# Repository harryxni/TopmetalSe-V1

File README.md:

# TopmetalSe-V1
This repo stores almost all of the info to run and understand the TopmetalSe

The directories here should be pretty self-explanatory honestly. 

If you want to learn how to run the chip, please look at Hardware and Firmware.

If you want to learn how well the chip performs and see examples, please look at Results.

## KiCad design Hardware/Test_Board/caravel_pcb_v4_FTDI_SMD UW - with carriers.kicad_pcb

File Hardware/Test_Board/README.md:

# Annotated PCB

In the annotated pcb image file, I have added some markers to explain any fixes that need to be made to the current test board. These are either where jumper cables must be soldered onto, or any components which should not be present.

On the left side of the board, the level shifters U12-U26 should not be used/soldered on. Instead, a jumper cable should be soldered between pads 3 and 4.

D4 should not be soldered on simply to remove a strong source of light which could ionize charge in the pixel array. It can useful to know if power is being supplied correctly, so use it in any initial testing phases. But, it should not be present for serious testing.

LA_Row_Clk should always be used and not Ser Tx (jumpered across).

VCCD should be connected to VCCD2 under the carrier board, so there should be a jumper wire between pins 43 and 27.

R23, R25 and R27 should not be present to prevent current flow along the voltage bias lines.

LDAC bar should always be jumpered.

The signals names for ROW and COL are actually switched. This is fixed in the FPGA software which controls these lines, but should be noted for any future iterations.

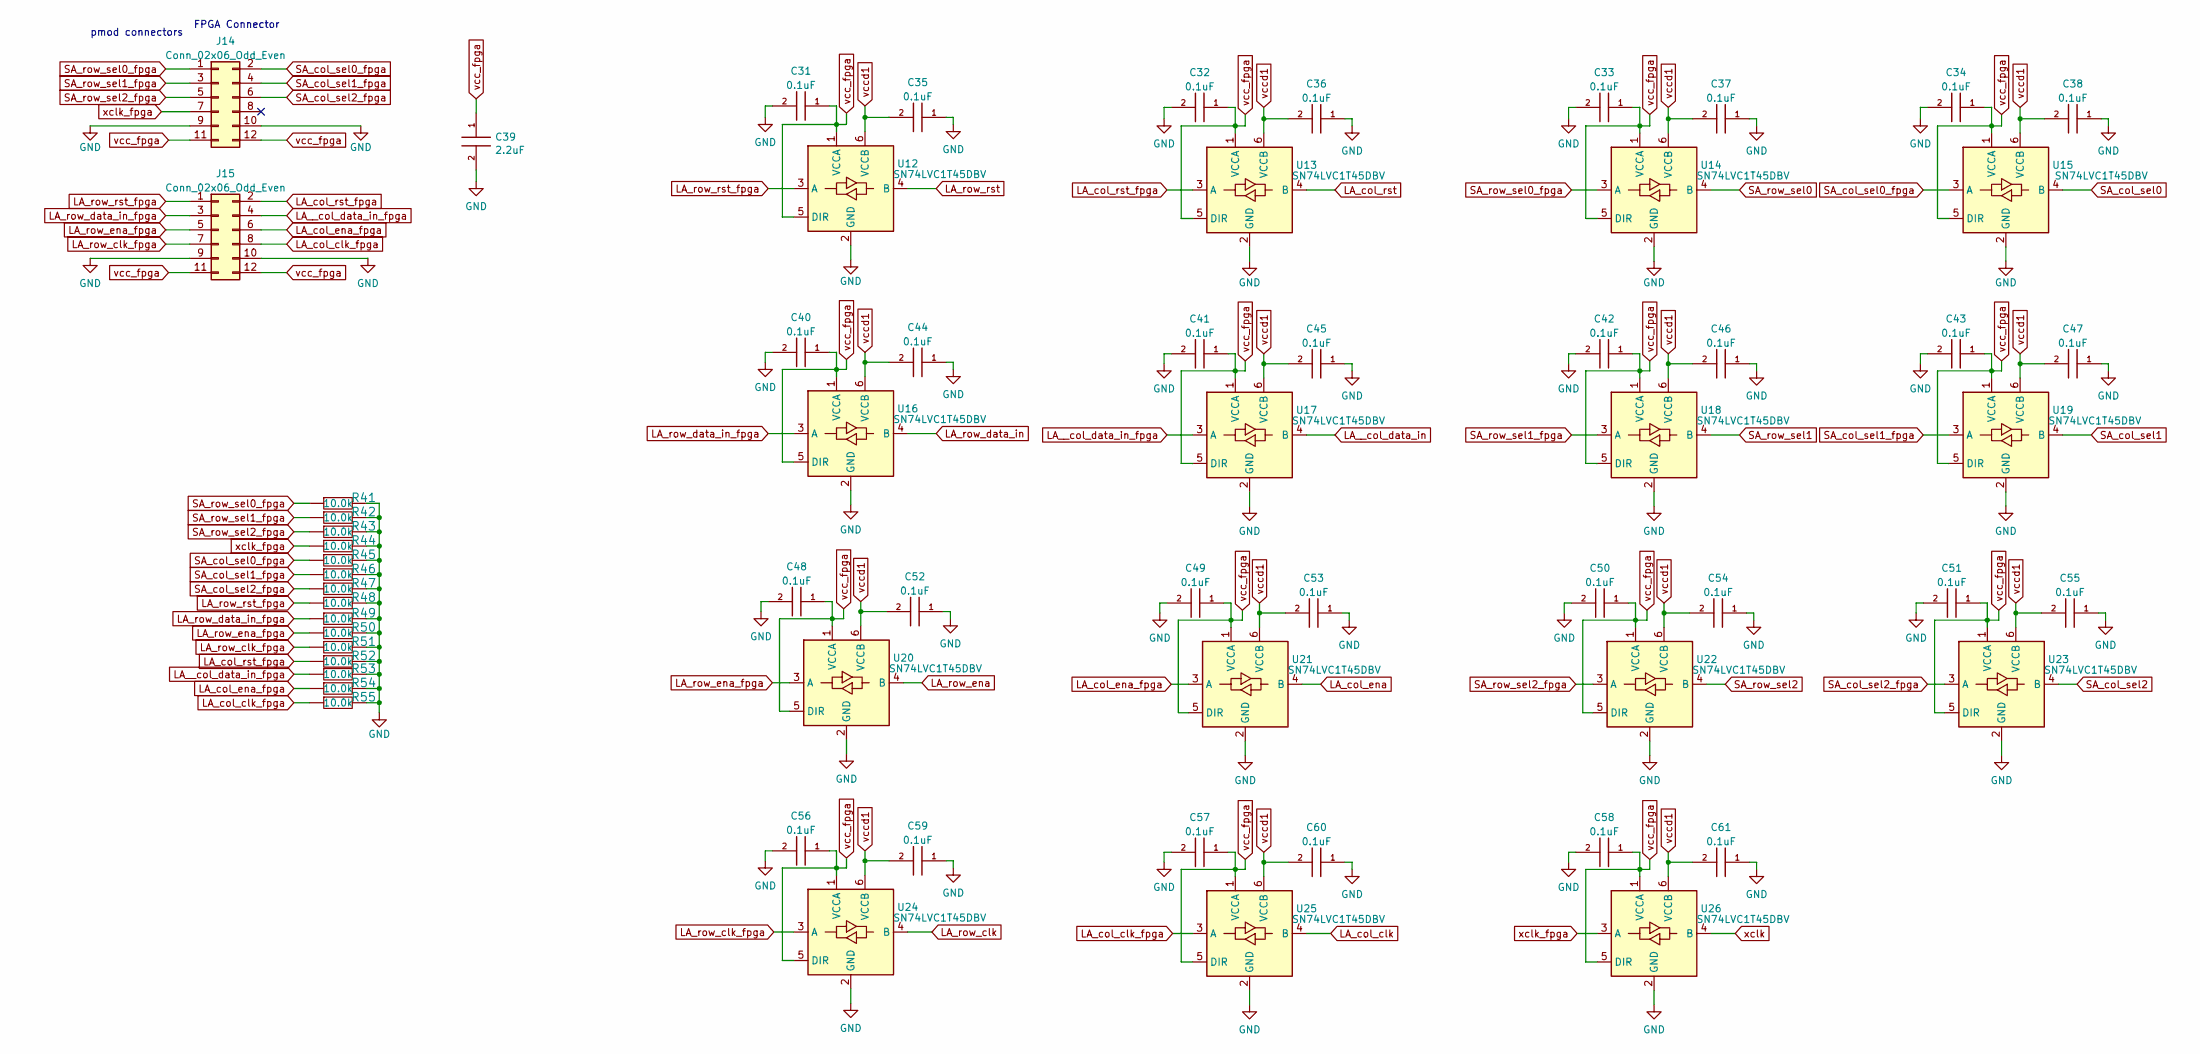
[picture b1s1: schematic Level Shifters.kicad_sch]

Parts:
C31, C32, C33, C34, C35, C36, C37, C38, C40, C41, C42, C43, C44, C45, C46, C47, C48, C49, C50, C51, C52, C53, C54, C55, C56, C57, C58, C59, C60, C61: 0.1uF; SM0603
C39: 2.2uF; SM0603
J14, J15: Conn_02x06_Odd_Even; PinHeader_2x06_P2.54mm_Horizontal
R41, R42, R43, R44, R45, R46, R47, R48, R49, R50, R51, R52, R53, R54, R55: 10.0k; SM0603
U12, U13, U14, U15, U16, U17, U18, U19, U20, U21, U22, U23, U24, U25, U26: SN74LVC1T45DBV; SOT-23-6

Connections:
LA__col_data_in: U17.4 (B); also elsewhere on the board
LA__col_data_in_fpga: J15.4, R53.1, U17.3 (A)
LA_col_clk: U25.4 (B); also elsewhere on the board
LA_col_clk_fpga: J15.8, R55.1, U25.3 (A)
LA_col_ena: U21.4 (B); also elsewhere on the board
LA_col_ena_fpga: J15.6, R54.1, U21.3 (A)
LA_col_rst: U13.4 (B); also elsewhere on the board
LA_col_rst_fpga: J15.2, R52.1, U13.3 (A)
LA_row_clk: U24.4 (B); also elsewhere on the board
LA_row_clk_fpga: J15.7, R51.1, U24.3 (A)
LA_row_data_in: U16.4 (B); also elsewhere on the board
LA_row_data_in_fpga: J15.3, R49.1, U16.3 (A)
LA_row_ena: U20.4 (B); also elsewhere on the board
LA_row_ena_fpga: J15.5, R50.1, U20.3 (A)
LA_row_rst: U12.4 (B); also elsewhere on the board
LA_row_rst_fpga: J15.1, R48.1, U12.3 (A)
SA_col_sel0: U15.4 (B); also elsewhere on the board
SA_col_sel0_fpga: J14.2, R45.1, U15.3 (A)
SA_col_sel1: U19.4 (B); also elsewhere on the board
SA_col_sel1_fpga: J14.4, R46.1, U19.3 (A)
SA_col_sel2: U23.4 (B); also elsewhere on the board
SA_col_sel2_fpga: J14.6, R47.1, U23.3 (A)
SA_row_sel0: U14.4 (B); also elsewhere on the board
SA_row_sel0_fpga: J14.1, R41.1, U14.3 (A)
SA_row_sel1: U18.4 (B); also elsewhere on the board
SA_row_sel1_fpga: J14.3, R42.1, U18.3 (A)
SA_row_sel2: U22.4 (B); also elsewhere on the board
SA_row_sel2_fpga: J14.5, R43.1, U22.3 (A)
vcc_fpga: C31.1, C32.1, C33.1, C34.1, C39.1, C40.1, C41.1, C42.1, C43.1, C48.1, C49.1, C50.1, C51.1, C56.1, C57.1, C58.1, J14.11, J14.12, J15.11, J15.12, U12.1 (VCCA), U12.5 (DIR), U13.1 (VCCA), U13.5 (DIR), U14.1 (VCCA), U14.5 (DIR), U15.1 (VCCA), U15.5 (DIR), U16.1 (VCCA), U16.5 (DIR), U17.1 (VCCA), U17.5 (DIR), U18.1 (VCCA), U18.5 (DIR), U19.1 (VCCA), U19.5 (DIR), U20.1 (VCCA), U20.5 (DIR), U21.1 (VCCA), U21.5 (DIR), U22.1 (VCCA), U22.5 (DIR), U23.1 (VCCA), U23.5 (DIR), U24.1 (VCCA), U24.5 (DIR), U25.1 (VCCA), U25.5 (DIR), U26.1 (VCCA), U26.5 (DIR)
vccd: C35.2, C36.2, C37.2, C38.2, C44.2, C45.2, C46.2, C47.2, C52.2, C53.2, C54.2, C55.2, C59.2, C60.2, C61.2, U12.6 (VCCB), U13.6 (VCCB), U14.6 (VCCB), U15.6 (VCCB), U16.6 (VCCB), U17.6 (VCCB), U18.6 (VCCB), U19.6 (VCCB), U20.6 (VCCB), U21.6 (VCCB), U22.6 (VCCB), U23.6 (VCCB), U24.6 (VCCB), U25.6 (VCCB), U26.6 (VCCB); also elsewhere on the board
xclk: U26.4 (B); also elsewhere on the board
xclk_fpga: J14.7, R44.1, U26.3 (A)

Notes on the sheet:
pmod connectors
FPGA Connector

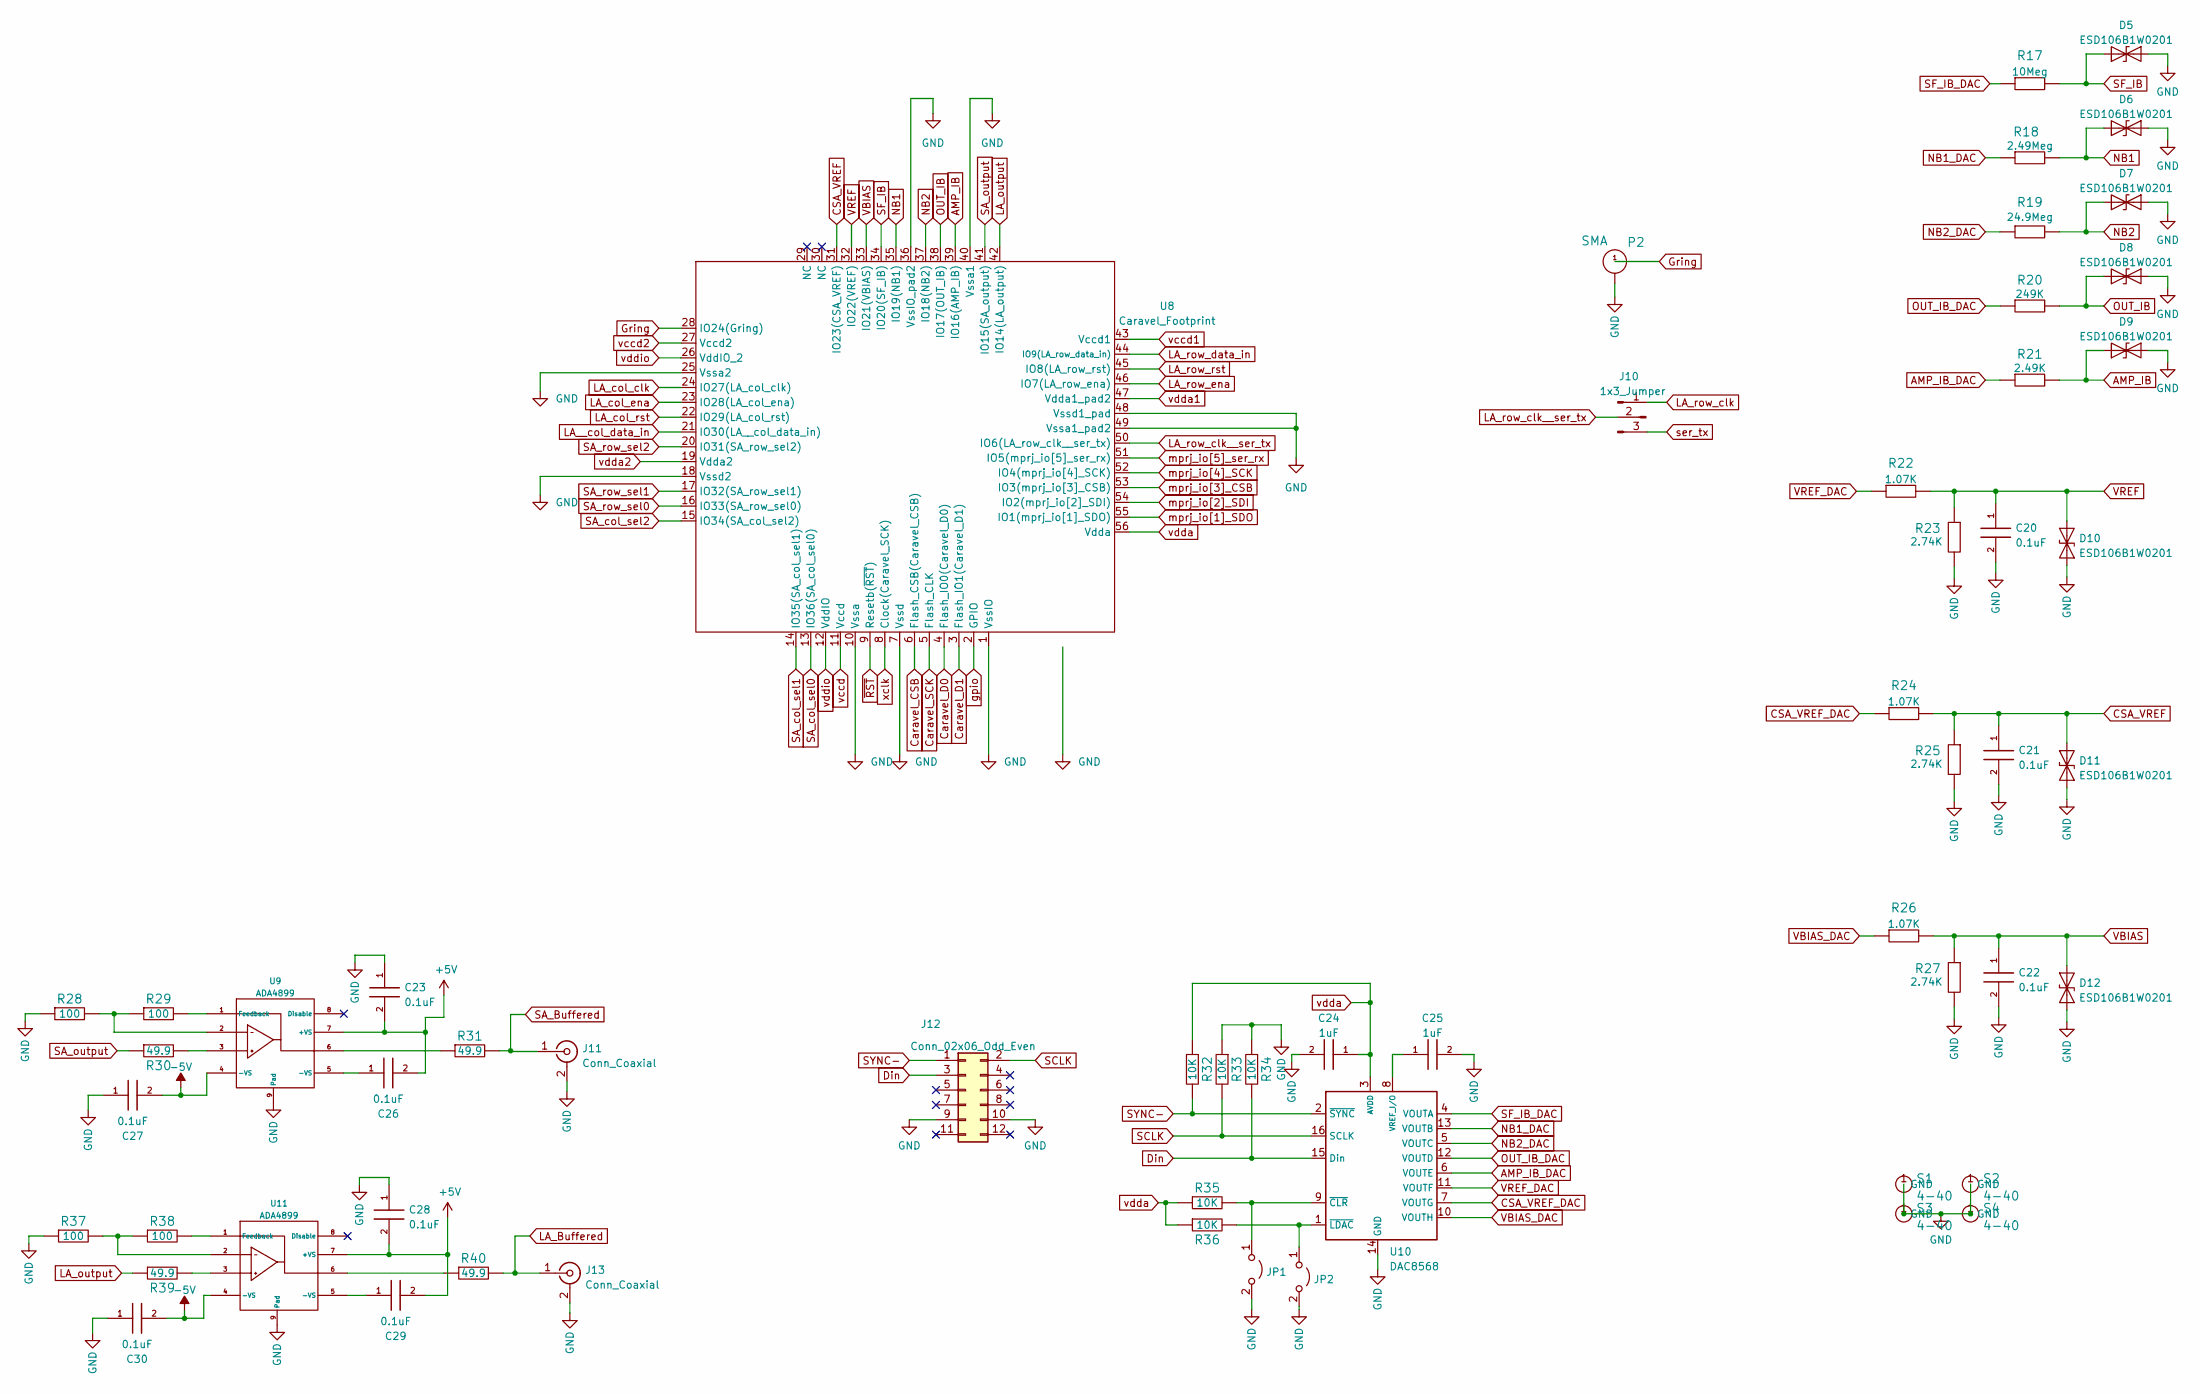
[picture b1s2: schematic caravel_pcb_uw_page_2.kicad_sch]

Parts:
C20, C21, C22, C23, C26, C27, C28, C29, C30: 0.1uF; SM0603
C24, C25: 1uF; SM0603
D5, D6, D7, D8, D9, D10, D11, D12: ESD106B1W0201; D_SOD-923
J10: 1x3_Jumper; SIL-3
J11, J13: Conn_Coaxial; SMA
J12: Conn_02x06_Odd_Even; PinHeader_2x06_P2.54mm_Horizontal
JP1, JP2: Jumper_2_Open; SIL-2
P2: SMA
R17: 10Meg; SM0603
R18: 2.49Meg; SM0603
R19: 24.9Meg; SM0603
R20: 249K; SM0603
R21: 2.49K; SM0603
R22, R24, R26: 1.07K; SM0603
R23, R25, R27: 2.74K; SM0603
R28, R29, R37, R38: 100; SM0603
R30, R31, R39, R40: 49.9; SM0603
R32, R33, R34, R35, R36: 10K; SM0603
S1, S2, S3, S4: 4-40; 4-40_Reduced
U8: Caravel_Footprint; Caravel_Carrier_Footprint
U9, U11: ADA4899; SO-8_EP
U10: DAC8568; TSSOP-16_4.4x5mm_P0.65mm

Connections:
AMP_IB: D9.1 (A1), R21.2, U8.39 (IO16(AMP_IB))
AMP_IB_DAC: R21.1, U10.6 (VOUTE)
CSA_VREF: C21.1, D11.1 (A1), R24.2, R25.1, U8.31 (IO23(CSA_VREF))
CSA_VREF_DAC: R24.1, U10.7 (VOUTG)
Caravel_CSB: U8.6 (Flash_CSB(Caravel_CSB)); also elsewhere on the board
Caravel_D0: U8.4 (Flash_IO0(Caravel_D0)); also elsewhere on the board
Caravel_D1: U8.3 (Flash_IO1(Caravel_D1)); also elsewhere on the board
Caravel_SCK: U8.5 (Flash_CLK); also elsewhere on the board
Din: J12.3, R34.2, U10.15 (Din)
Gring: P2.1, U8.28 (IO24(Gring))
LA_Buffered: J13.1 (In), R40.2
LA__col_data_in: U8.21 (IO30(LA__col_data_in)); also elsewhere on the board
LA_col_clk: U8.24 (IO27(LA_col_clk)); also elsewhere on the board
LA_col_ena: U8.23 (IO28(LA_col_ena)); also elsewhere on the board
LA_col_rst: U8.22 (IO29(LA_col_rst)); also elsewhere on the board
LA_output: R39.1, U8.42 (IO14(LA_output))
LA_row_clk: J10.1; also elsewhere on the board
LA_row_clk__ser_tx: J10.2, U8.50 (IO6(LA_row_clk__ser_tx))
LA_row_data_in: U8.44 (IO9(LA_row_data_in)); also elsewhere on the board
LA_row_ena: U8.46 (IO7(LA_row_ena)); also elsewhere on the board
LA_row_rst: U8.45 (IO8(LA_row_rst)); also elsewhere on the board
NB1: D6.1 (A1), R18.2, U8.35 (IO19(NB1))
NB1_DAC: R18.1, U10.13 (VOUTB)
NB2: D7.1 (A1), R19.2, U8.37 (IO18(NB2))
NB2_DAC: R19.1, U10.5 (VOUTC)
unnamed: C25.1, U10.8 (VREF_I/O)
unnamed: C26.1, U9.5 (-VS)
unnamed: C29.1, U11.5 (-VS)
unnamed: JP1.1 (A), R35.2, U10.9 (~CLR)
unnamed: JP2.1 (A), R36.2, U10.1 (~LDAC)
unnamed: R28.2, R29.1, U9.2
unnamed: R29.2, U9.1 (Feedback)
unnamed: R30.2, U9.3
unnamed: R31.1, U9.6
unnamed: R37.2, R38.1, U11.2
unnamed: R38.2, U11.1 (Feedback)
unnamed: R39.2, U11.3
unnamed: R40.1, U11.6
OUT_IB: D8.1 (A1), R20.2, U8.38 (IO17(OUT_IB))
OUT_IB_DAC: R20.1, U10.12 (VOUTD)
SA_Buffered: J11.1 (In), R31.2
SA_col_sel0: U8.13 (IO36(SA_col_sel0)); also elsewhere on the board
SA_col_sel1: U8.14 (IO35(SA_col_sel1)); also elsewhere on the board
SA_col_sel2: U8.15 (IO34(SA_col_sel2)); also elsewhere on the board
SA_output: R30.1, U8.41 (IO15(SA_output))
SA_row_sel0: U8.16 (IO33(SA_row_sel0)); also elsewhere on the board
SA_row_sel1: U8.17 (IO32(SA_row_sel1)); also elsewhere on the board
SA_row_sel2: U8.20 (IO31(SA_row_sel2)); also elsewhere on the board
SCLK: J12.2, R33.2, U10.16 (SCLK)
SF_IB: D5.1 (A1), R17.2, U8.34 (IO20(SF_IB))
SF_IB_DAC: R17.1, U10.4 (VOUTA)
SYNC-: J12.1, R32.2, U10.2 (~SYNC)
USB_CS1: U8.53 (IO3(mprj_io[3]_CSB)); also elsewhere on the board
USB_SCK_TXD: U8.52 (IO4(mprj_io[4]_SCK)); also elsewhere on the board
USB_SI: U8.55 (IO1(mprj_io[1]_SDO)); also elsewhere on the board
USB_SO_RXD: U8.54 (IO2(mprj_io[2]_SDI)); also elsewhere on the board
VBIAS: C22.1, D12.1 (A1), R26.2, R27.1, U8.33 (IO21(VBIAS))
VBIAS_DAC: R26.1, U10.10 (VOUTH)
VREF: C20.1, D10.1 (A1), R22.2, R23.1, U8.32 (IO22(VREF))
VREF_DAC: R22.1, U10.11 (VOUTF)
gpio: U8.2 (GPIO); also elsewhere on the board
mprj_io[5]_ser_rx: U8.51 (IO5(mprj_io[5]_ser_rx)); also elsewhere on the board
ser_tx: J10.3; also elsewhere on the board
vccd: U8.11 (Vccd), U8.43 (Vccd1); also elsewhere on the board
vccd2: U8.27 (Vccd2)
vdda1: U8.47 (Vdda1_pad2)
vdda2: U8.19 (Vdda2)
xclk: U8.8 (Clock(Caravel_SCK)); also elsewhere on the board
~RST: U8.9 (Resetb(~RST)); also elsewhere on the board

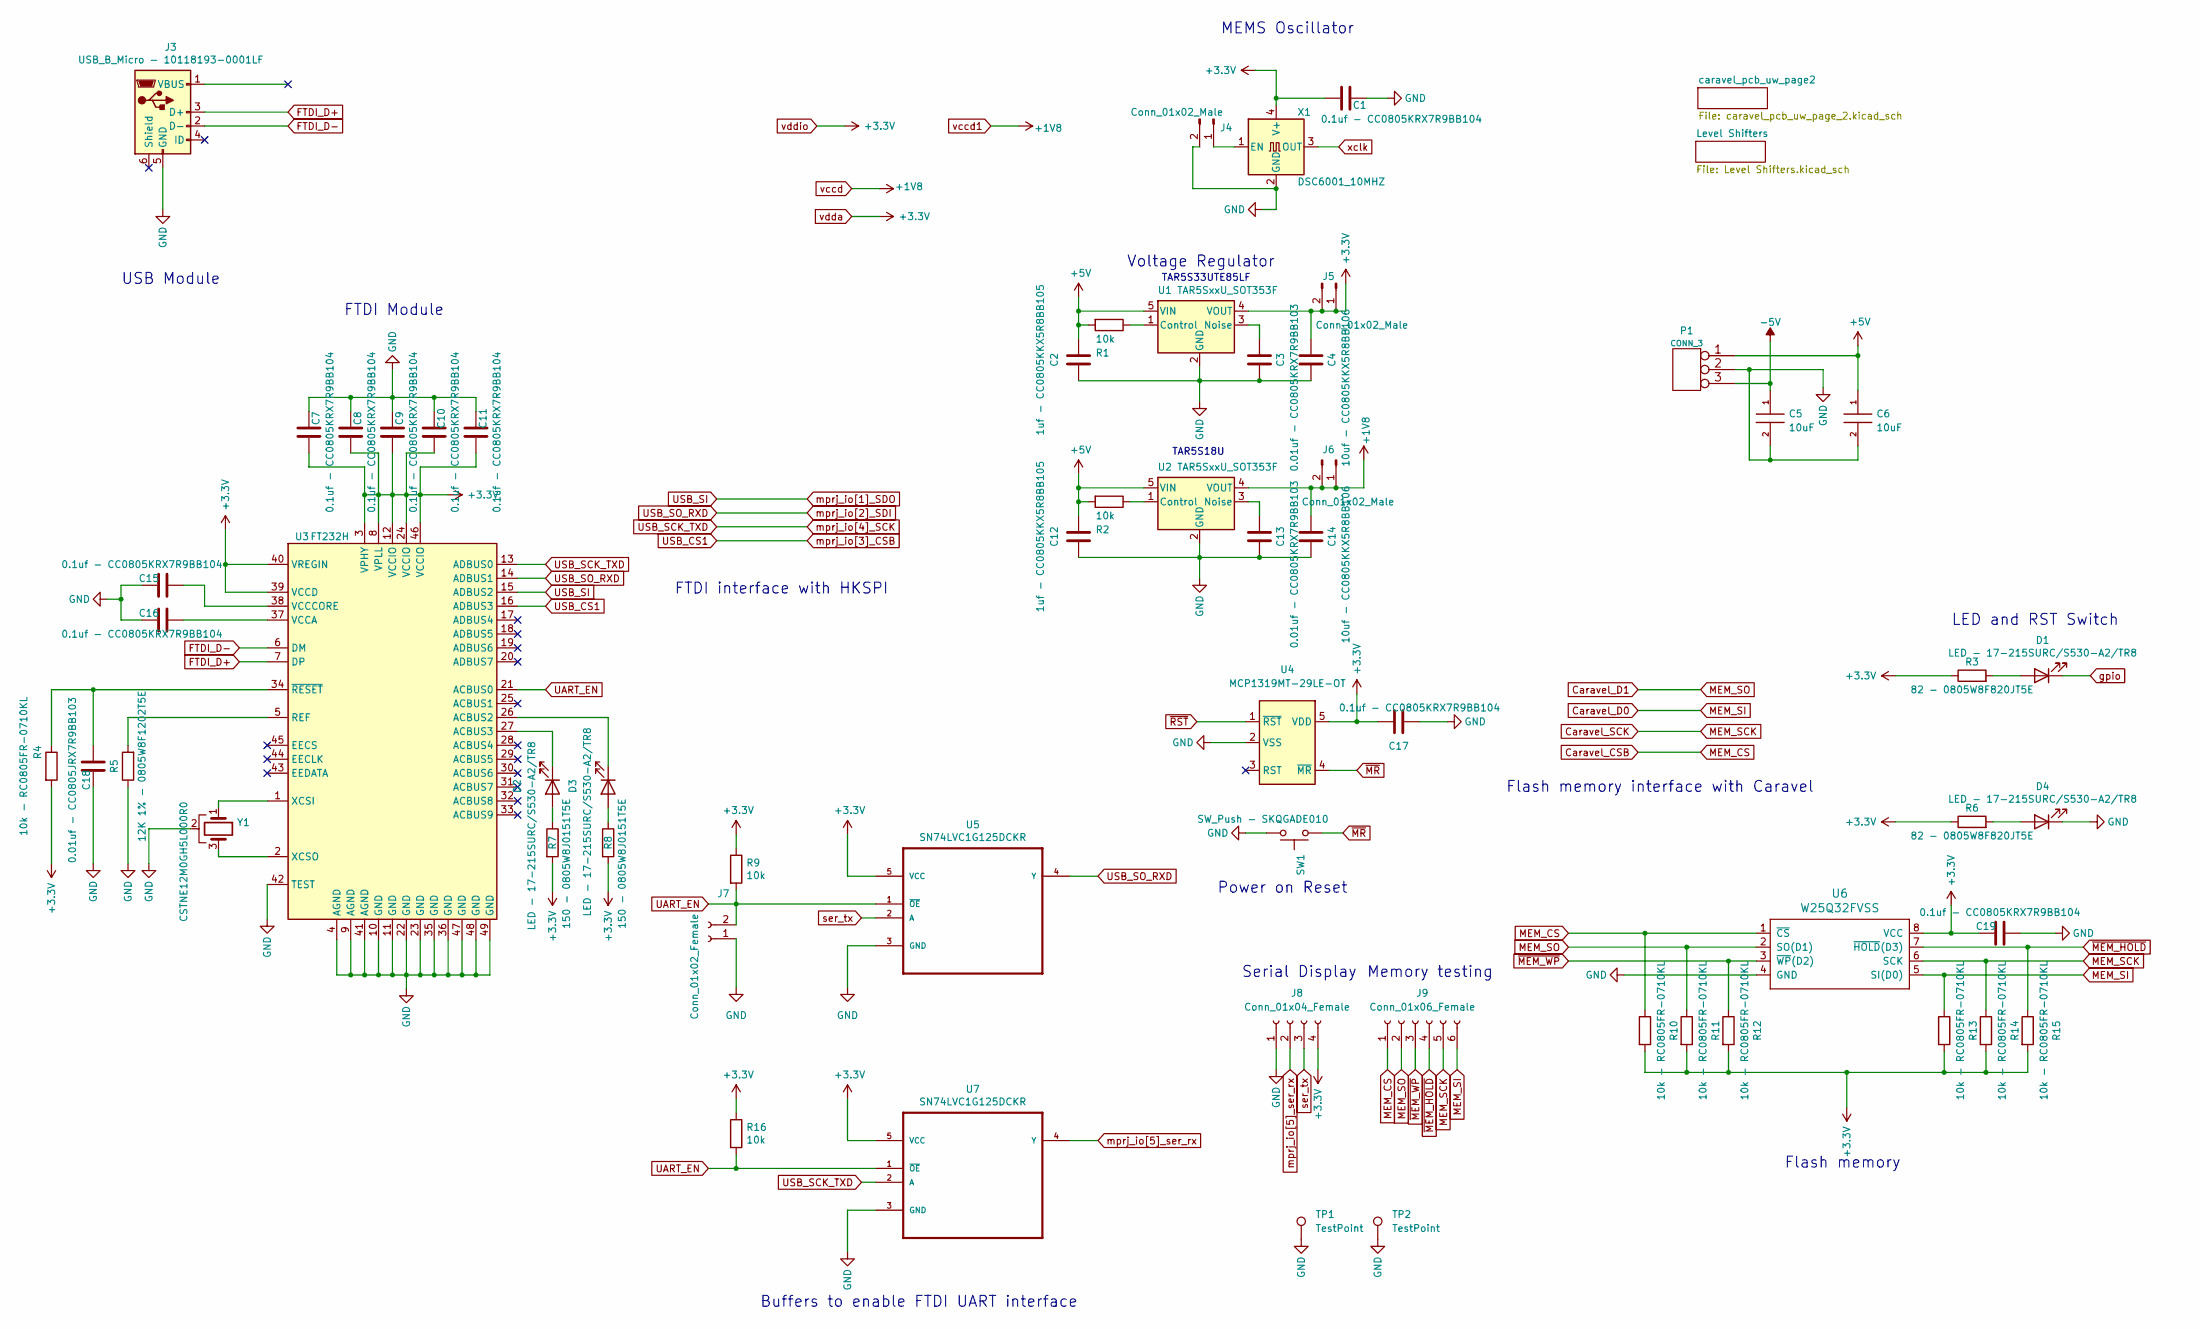
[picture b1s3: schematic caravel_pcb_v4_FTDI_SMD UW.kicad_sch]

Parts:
C1, C7, C8, C10, C11, C15, C16, C17, C19: 0.1uf - CC0805KRX7R9BB104; SM0603
C2, C12: 1uf - CC0805KKX5R8BB105; SM0603
C3, C13: 0.01uf - CC0805KRX7R9BB103; SM0603
C4, C14: 10uf - CC0805KKX5R8BB106; SM0603
C5, C6: 10uF; SM0603
C9: 0.1uf - CC0805KRX7R9BB104; SM0402
C18: 0.01uf - CC0805JRX7R9BB103; SM0603
D1, D2, D3, D4: LED - 17-215SURC/S530-A2/TR8; LED_1206_3216Metric
J3: USB_B_Micro - 10118193-0001LF; FCI_10118193-0001LF
J4, J5, J6: Conn_01x02_Male; PinHeader_1x02_P2.54mm_Vertical
J7: Conn_01x02_Female; PinHeader_1x02_P2.54mm_Vertical
J8: Conn_01x04_Female; PinHeader_1x04_P2.54mm_Vertical
J9: Conn_01x06_Female; PinHeader_1x06_P2.54mm_Vertical
P1: CONN_3; SIL-3_RA
R1, R2, R9, R16: 10k; SM0603
R3, R6: 82 - 0805W8F820JT5E; SM0603
R4, R10, R11, R12, R13, R14, R15: 10k - RC0805FR-0710KL; SM0603
R5: 12K 1% - 0805W8F1202T5E; SM0402
R7, R8: 150 - 0805W8J0151T5E; SM0603
SW1: SW_Push - SKQGADE010; SW4-SMD-5.2X5.2X1.5MM
TP1, TP2: TestPoint; TestPoint_Bridge_Pitch2.54mm_Drill1.0mm
U1, U2: TAR5SxxU_SOT353F; SOT-353_SC-70-5_Handsoldering
U3: FT232H; QFN-48-1EP_8x8mm_P0.5mm_EP6.2x6.2mm
U4: MCP1319MT-29LE-OT; SOT23-5
U5, U7: SN74LVC1G125DCKR; SOT23-5
U6: W25Q32FVSS; SOIC127P790X216-8N
X1: DSC6001_10MHZ; DSC6001JE1A-010.0000
Y1: CSTNE12M0GH5L000R0

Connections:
/Vdda: U1.56 (Vdda); also elsewhere on the board
Caravel_CSB: J9.1, R10.1, U6.1 (~CS); also elsewhere on the board
Caravel_D0: J9.6, R13.1, U6.5 (SI(D0)); also elsewhere on the board
Caravel_D1: J9.2, R11.1, U6.2 (SO(D1)); also elsewhere on the board
Caravel_SCK: J9.5, R14.1, U6.6 (SCK); also elsewhere on the board
FTDI_D+: J3.3 (D+), U3.7 (DP)
FTDI_D-: J3.2 (D-), U3.6 (DM)
unnamed: C13.1, U2.3 (Noise)
unnamed: C15.2, U3.38 (VCCCORE)
unnamed: C16.2, U3.37 (VCCA)
unnamed: C18.2, R4.1, U3.34 (~RESET)
unnamed: D1.2 (A), R3.2
unnamed: D2.1 (K), U3.27 (ACBUS3)
unnamed: D2.2 (A), R7.1
unnamed: D3.1 (K), U3.26 (ACBUS2)
unnamed: D3.2 (A), R8.1
unnamed: D4.2 (A), R6.2
unnamed: J4.1, X1.1 (EN)
unnamed: R2.1, U2.1 (Control)
unnamed: R5.2, U3.5 (REF)
unnamed 62: U1.VssIO; also elsewhere on the board
unnamed 63: U1.6 (Flash_CSB(Caravel_CSB)), U1.Flash_CSB (Flash_CSB(Caravel_CSB)); also elsewhere on the board
unnamed 64: U1.Vssd; also elsewhere on the board
unnamed 65: U1.8 (Clock(Caravel_SCK)), U1.Clock (Clock(Caravel_SCK)); also elsewhere on the board
unnamed 66: U1.9 (Resetb(~RST)), U1.Resetb (Resetb(~RST)); also elsewhere on the board
unnamed 67: U1.Vssa; also elsewhere on the board
unnamed 68: U1.Vccd; also elsewhere on the board
unnamed 69: U1.VddIO; also elsewhere on the board
unnamed 70: U1.13 (IO36(SA_col_sel0)), U1.IO36 (IO36(SA_col_sel0)); also elsewhere on the board
unnamed 71: U1.14 (IO35(SA_col_sel1)), U1.IO35 (IO35(SA_col_sel1)); also elsewhere on the board
unnamed 72: U1.15 (IO34(SA_col_sel2)), U1.IO34 (IO34(SA_col_sel2)); also elsewhere on the board
unnamed 73: U1.16 (IO33(SA_row_sel0)), U1.IO33 (IO33(SA_row_sel0)); also elsewhere on the board
unnamed 74: U1.17 (IO32(SA_row_sel1)), U1.IO32 (IO32(SA_row_sel1)); also elsewhere on the board
unnamed 75: U1.Vssd2; also elsewhere on the board
unnamed 76: U1.Vdda2; also elsewhere on the board
unnamed 77: U1.20 (IO31(SA_row_sel2)), U1.IO31 (IO31(SA_row_sel2)); also elsewhere on the board
unnamed 78: U1.21 (IO30(LA__col_data_in)), U1.IO30 (IO30(LA__col_data_in)); also elsewhere on the board
unnamed 79: U1.22 (IO29(LA_col_rst)), U1.IO29 (IO29(LA_col_rst)); also elsewhere on the board
unnamed 80: U1.23 (IO28(LA_col_ena)), U1.IO28 (IO28(LA_col_ena)); also elsewhere on the board
unnamed 81: U1.24 (IO27(LA_col_clk)), U1.IO27 (IO27(LA_col_clk)); also elsewhere on the board
unnamed 82: U1.Vssa2; also elsewhere on the board
unnamed 83: U1.VddIO_2; also elsewhere on the board
unnamed 84: U1.Vccd2; also elsewhere on the board
unnamed 85: U1.28 (IO24(Gring)), U1.IO24 (IO24(Gring)); also elsewhere on the board
unnamed 86: U1.31 (IO23(CSA_VREF)), U1.IO23 (IO23(CSA_VREF)); also elsewhere on the board
unnamed 87: U1.32 (IO22(VREF)), U1.IO22 (IO22(VREF)); also elsewhere on the board
unnamed 88: U1.33 (IO21(VBIAS)), U1.IO21 (IO21(VBIAS)); also elsewhere on the board
unnamed 89: U1.34 (IO20(SF_IB)), U1.IO20 (IO20(SF_IB)); also elsewhere on the board
unnamed 90: U1.35 (IO19(NB1)), U1.IO19 (IO19(NB1)); also elsewhere on the board
unnamed 91: U1.VssIO_pad2; also elsewhere on the board
unnamed 92: U1.37 (IO18(NB2)), U1.IO18 (IO18(NB2)); also elsewhere on the board
unnamed 93: U1.38 (IO17(OUT_IB)), U1.IO17 (IO17(OUT_IB)); also elsewhere on the board
unnamed 94: U1.39 (IO16(AMP_IB)), U1.IO16 (IO16(AMP_IB)); also elsewhere on the board
unnamed 95: U1.Vssa1; also elsewhere on the board
unnamed 96: U1.41 (IO15(SA_output)), U1.IO15 (IO15(SA_output)); also elsewhere on the board
unnamed 97: U1.42 (IO14(LA_output)), U1.IO14 (IO14(LA_output)); also elsewhere on the board
unnamed 98: U1.Vccd1; also elsewhere on the board
unnamed 99: U1.44 (IO9(LA_row_data_in)), U1.IO9 (IO9(LA_row_data_in)); also elsewhere on the board
unnamed 100: U1.45 (IO8(LA_row_rst)), U1.IO8 (IO8(LA_row_rst)); also elsewhere on the board
unnamed 101: U1.46 (IO7(LA_row_ena)), U1.IO7 (IO7(LA_row_ena)); also elsewhere on the board
unnamed 102: U1.Vdda1_pad2; also elsewhere on the board
unnamed 103: U1.Vssd1_pad; also elsewhere on the board
unnamed 104: U1.Vssa1_pad2; also elsewhere on the board
unnamed 105: U1.50 (IO6(LA_row_clk__ser_tx)), U1.IO6 (IO6(LA_row_clk__ser_tx)); also elsewhere on the board
unnamed 106: U1.51 (IO5(mprj_io[5]_ser_rx)), U1.IO5 (IO5(mprj_io[5]_ser_rx)); also elsewhere on the board
unnamed 107: U1.52 (IO4(mprj_io[4]_SCK)), U1.IO4 (IO4(mprj_io[4]_SCK)); also elsewhere on the board
unnamed 108: U1.53 (IO3(mprj_io[3]_CSB)), U1.IO3 (IO3(mprj_io[3]_CSB)); also elsewhere on the board
unnamed 109: U1.54 (IO2(mprj_io[2]_SDI)), U1.IO2 (IO2(mprj_io[2]_SDI)); also elsewhere on the board
unnamed 110: U1.55 (IO1(mprj_io[1]_SDO)), U1.IO1 (IO1(mprj_io[1]_SDO)); also elsewhere on the board
unnamed 111: U1.Vdda; also elsewhere on the board
unnamed: U3.1 (XCSI), Y1.1
unnamed: U3.2 (XCSO), Y1.3
UART_EN: J7.2, R9.2, R16.2, U3.21 (ACBUS0), U5.1 (~OE), U7.1 (~OE)
USB_CS1: U3.16 (ADBUS3); also elsewhere on the board
USB_SCK_TXD: U3.13 (ADBUS0), U7.2 (A); also elsewhere on the board
USB_SI: U3.15 (ADBUS2); also elsewhere on the board
USB_SO_RXD: U3.14 (ADBUS1), U5.4 (Y); also elsewhere on the board
gpio: D1.1 (K); also elsewhere on the board
mprj_io[5]_ser_rx: J8.2, U7.4 (Y); also elsewhere on the board
ser_tx: J8.3, U5.2 (A); also elsewhere on the board
vccd: C14.2, J6.1, J6.2, U2.4 (VOUT); also elsewhere on the board
xclk: X1.3 (OUT); also elsewhere on the board
~MEM_HOLD: J9.4, R15.1, U6.7 (~HOLD(D3))
~MEM_WP: J9.3, R12.1, U6.3 (~WP(D2))
~MR: SW1.1, U4.4 (~MR)
~RST: U4.1 (~RST); also elsewhere on the board

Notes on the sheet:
Serial Display
LED and RST Switch
Flash memory interface with Caravel
Power on Reset
Flash memory
Memory testing
FTDI interface with HKSPI
TAR5S33UTE85LF
Voltage Regulator
FTDI Module
USB Module
TAR5S18U
MEMS Oscillator
Buffers to enable FTDI UART interface

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
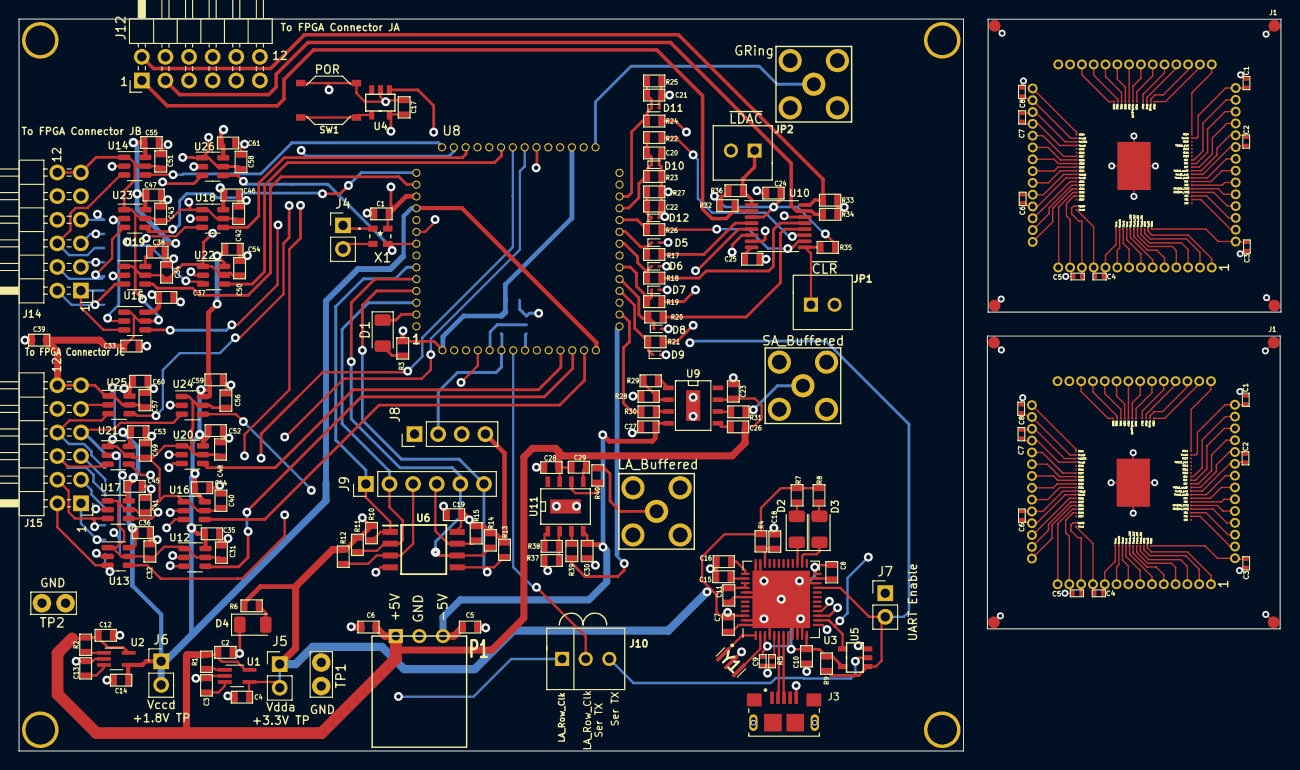
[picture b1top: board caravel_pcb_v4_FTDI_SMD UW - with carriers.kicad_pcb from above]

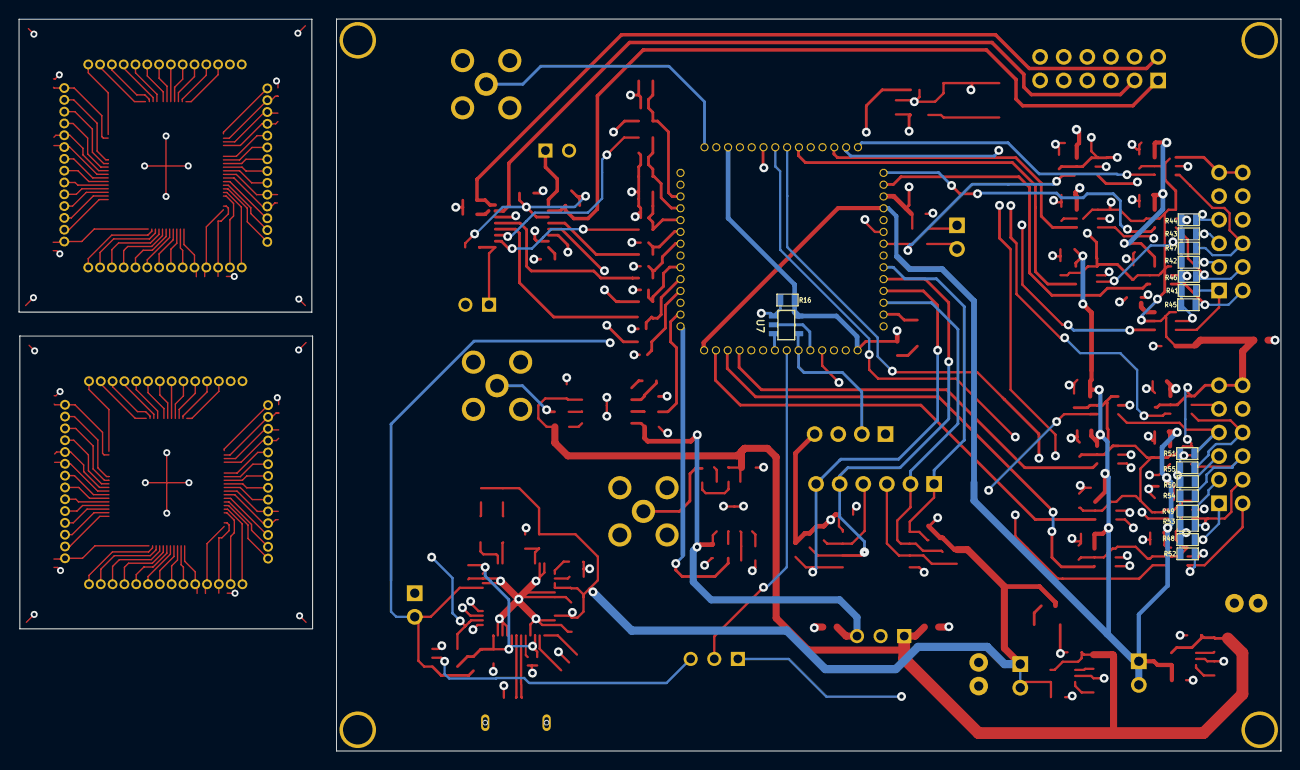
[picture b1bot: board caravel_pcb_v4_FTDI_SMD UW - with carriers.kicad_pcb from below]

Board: 4 copper layers, 135.7 x 78.7 mm, 206 parts (17 on the bottom side), 171 nets.

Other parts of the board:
C1#2, C7#3, C8#2: 0.1uf - CC0805KRX7R9BB104; SM0603
C1#3, C2#3, C3#2, C3#3, C4#3, C5#2, C6#3, C7#2, C8#3: 0.1uF; SM0402
C2#2: 1uf - CC0805KKX5R8BB105; SM0603
C4#2: 10uf - CC0805KKX5R8BB106; SM0603
C5#3, C6#2: 10uF; SM0603
J1, J1#2, J2, J2#2, J3#2, J3#3, J4#2, J4#3: Shield_Pad; .050_Pad_TP
U1#2: TAR5SxxU_SOT353F; SOT-353_SC-70-5_Handsoldering
U1#3: Caravel_Carrier

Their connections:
/Vdda: C3#2.1, C3#3.1, U1#3.56 (Vdda); also elsewhere on the board
unnamed 62: U1#3.VssIO; also elsewhere on the board
unnamed 63: U1#3.6 (Flash_CSB(Caravel_CSB)), U1#3.Flash_CSB (Flash_CSB(Caravel_CSB)); also elsewhere on the board
unnamed 64: U1#3.Vssd; also elsewhere on the board
unnamed 65: U1#3.8 (Clock(Caravel_SCK)), U1#3.Clock (Clock(Caravel_SCK)); also elsewhere on the board
unnamed 66: U1#3.9 (Resetb(~RST)), U1#3.Resetb (Resetb(~RST)); also elsewhere on the board
unnamed 67: U1#3.Vssa; also elsewhere on the board
unnamed 68: U1#3.Vccd; also elsewhere on the board
unnamed 69: U1#3.VddIO; also elsewhere on the board
unnamed 70: U1#3.13 (IO36(SA_col_sel0)), U1#3.IO36 (IO36(SA_col_sel0)); also elsewhere on the board
unnamed 71: U1#3.14 (IO35(SA_col_sel1)), U1#3.IO35 (IO35(SA_col_sel1)); also elsewhere on the board
unnamed 72: U1#3.15 (IO34(SA_col_sel2)), U1#3.IO34 (IO34(SA_col_sel2)); also elsewhere on the board
unnamed 73: U1#3.16 (IO33(SA_row_sel0)), U1#3.IO33 (IO33(SA_row_sel0)); also elsewhere on the board
unnamed 74: U1#3.17 (IO32(SA_row_sel1)), U1#3.IO32 (IO32(SA_row_sel1)); also elsewhere on the board
unnamed 75: U1#3.Vssd2; also elsewhere on the board
unnamed 76: U1#3.Vdda2; also elsewhere on the board
unnamed 77: U1#3.20 (IO31(SA_row_sel2)), U1#3.IO31 (IO31(SA_row_sel2)); also elsewhere on the board
unnamed 78: U1#3.21 (IO30(LA__col_data_in)), U1#3.IO30 (IO30(LA__col_data_in)); also elsewhere on the board
unnamed 79: U1#3.22 (IO29(LA_col_rst)), U1#3.IO29 (IO29(LA_col_rst)); also elsewhere on the board
unnamed 80: U1#3.23 (IO28(LA_col_ena)), U1#3.IO28 (IO28(LA_col_ena)); also elsewhere on the board
unnamed 81: U1#3.24 (IO27(LA_col_clk)), U1#3.IO27 (IO27(LA_col_clk)); also elsewhere on the board
unnamed 82: U1#3.Vssa2; also elsewhere on the board
unnamed 83: U1#3.VddIO_2; also elsewhere on the board
unnamed 84: U1#3.Vccd2; also elsewhere on the board
unnamed 85: U1#3.28 (IO24(Gring)), U1#3.IO24 (IO24(Gring)); also elsewhere on the board
unnamed 86: U1#3.31 (IO23(CSA_VREF)), U1#3.IO23 (IO23(CSA_VREF)); also elsewhere on the board
unnamed 87: U1#3.32 (IO22(VREF)), U1#3.IO22 (IO22(VREF)); also elsewhere on the board
unnamed 88: U1#3.33 (IO21(VBIAS)), U1#3.IO21 (IO21(VBIAS)); also elsewhere on the board
unnamed 89: U1#3.34 (IO20(SF_IB)), U1#3.IO20 (IO20(SF_IB)); also elsewhere on the board
unnamed 90: U1#3.35 (IO19(NB1)), U1#3.IO19 (IO19(NB1)); also elsewhere on the board
unnamed 91: U1#3.VssIO_pad2; also elsewhere on the board
unnamed 92: U1#3.37 (IO18(NB2)), U1#3.IO18 (IO18(NB2)); also elsewhere on the board
unnamed 93: U1#3.38 (IO17(OUT_IB)), U1#3.IO17 (IO17(OUT_IB)); also elsewhere on the board
unnamed 94: U1#3.39 (IO16(AMP_IB)), U1#3.IO16 (IO16(AMP_IB)); also elsewhere on the board
unnamed 95: U1#3.Vssa1; also elsewhere on the board
unnamed 96: U1#3.41 (IO15(SA_output)), U1#3.IO15 (IO15(SA_output)); also elsewhere on the board
unnamed 97: U1#3.42 (IO14(LA_output)), U1#3.IO14 (IO14(LA_output)); also elsewhere on the board
unnamed 98: U1#3.Vccd1; also elsewhere on the board
unnamed 99: U1#3.44 (IO9(LA_row_data_in)), U1#3.IO9 (IO9(LA_row_data_in)); also elsewhere on the board
unnamed 100: U1#3.45 (IO8(LA_row_rst)), U1#3.IO8 (IO8(LA_row_rst)); also elsewhere on the board
unnamed 101: U1#3.46 (IO7(LA_row_ena)), U1#3.IO7 (IO7(LA_row_ena)); also elsewhere on the board
unnamed 102: U1#3.Vdda1_pad2; also elsewhere on the board
unnamed 103: U1#3.Vssd1_pad; also elsewhere on the board
unnamed 104: U1#3.Vssa1_pad2; also elsewhere on the board
unnamed 105: U1#3.50 (IO6(LA_row_clk__ser_tx)), U1#3.IO6 (IO6(LA_row_clk__ser_tx)); also elsewhere on the board
unnamed 106: U1#3.51 (IO5(mprj_io[5]_ser_rx)), U1#3.IO5 (IO5(mprj_io[5]_ser_rx)); also elsewhere on the board
unnamed 107: U1#3.52 (IO4(mprj_io[4]_SCK)), U1#3.IO4 (IO4(mprj_io[4]_SCK)); also elsewhere on the board
unnamed 108: U1#3.53 (IO3(mprj_io[3]_CSB)), U1#3.IO3 (IO3(mprj_io[3]_CSB)); also elsewhere on the board
unnamed 109: U1#3.54 (IO2(mprj_io[2]_SDI)), U1#3.IO2 (IO2(mprj_io[2]_SDI)); also elsewhere on the board
unnamed 110: U1#3.55 (IO1(mprj_io[1]_SDO)), U1#3.IO1 (IO1(mprj_io[1]_SDO)); also elsewhere on the board
unnamed 111: U1#3.Vdda; also elsewhere on the board

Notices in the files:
parts and their libraries:
Copyright 2016 Accelerated Designs. All rights reserved.
